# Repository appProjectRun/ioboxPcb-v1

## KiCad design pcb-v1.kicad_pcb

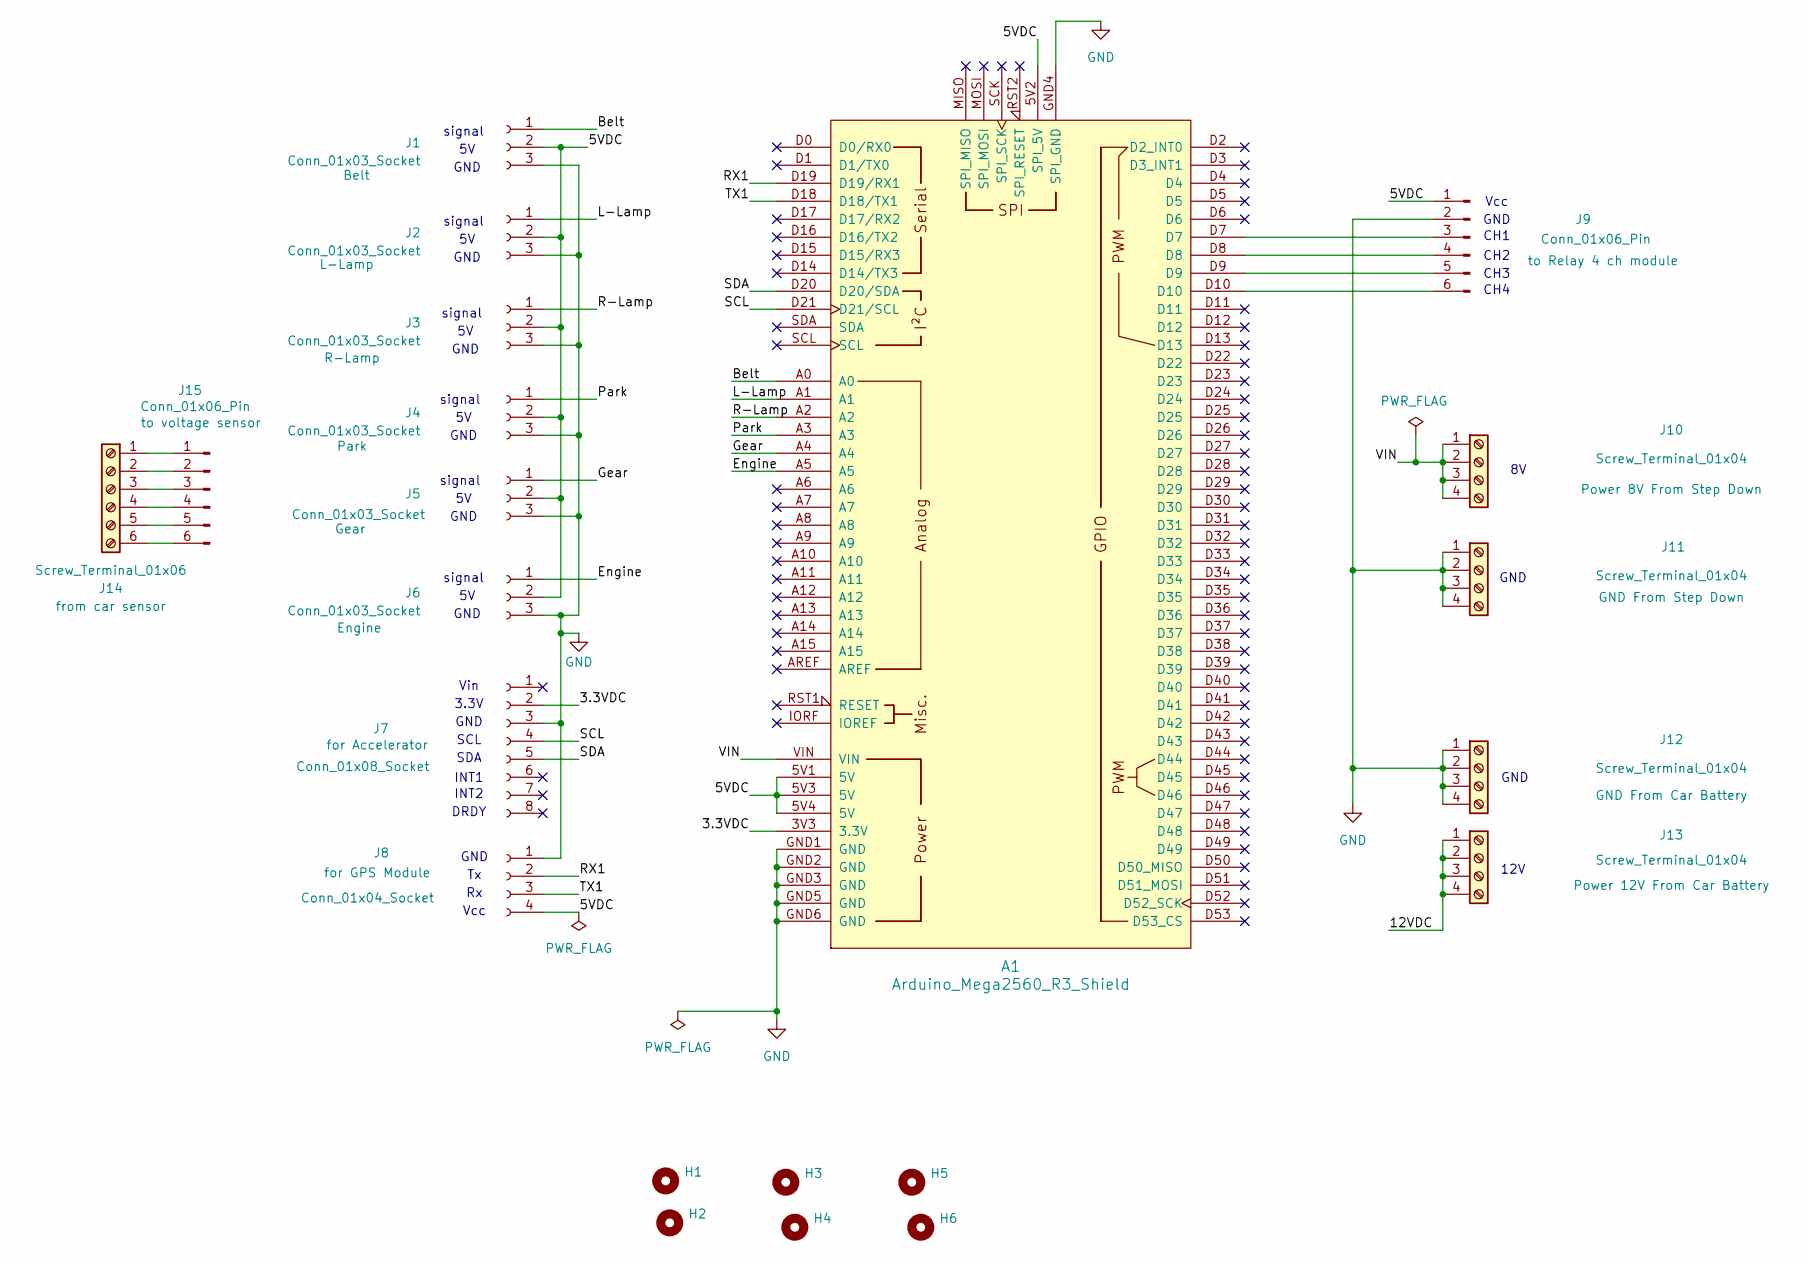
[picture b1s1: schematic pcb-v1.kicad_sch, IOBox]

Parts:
A1: Arduino_Mega2560_R3_Shield
H1, H2, H3, H4, H5, H6: MountingHole; MountingHole_4.5mm
J1, J2, J3, J4, J5, J6: Conn_01x03_Socket; PinSocket_1x03_P2.54mm_Vertical
J7: Conn_01x08_Socket; PinSocket_1x08_P2.54mm_Vertical
J8: Conn_01x04_Socket; PinSocket_1x04_P2.54mm_Vertical
J9, J15: Conn_01x06_Pin; Molex_SPOX_5267-06A_1x06_P2.50mm_Vertical
J10, J11, J12, J13: Screw_Terminal_01x04; TerminalBlock_bornier-4_P5.08mm
J14: Screw_Terminal_01x06; TerminalBlock_bornier-6_P5.08mm

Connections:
/3.3VDC: A1.3V3 (3.3V), J7.2
/5VDC: A1.5V1 (5V), A1.5V2 (SPI_5V), A1.5V3 (5V), A1.5V4 (5V), J1.2, J2.2, J3.2, J4.2, J5.2, J6.2, J8.4, J9.1
/12VDC: J13.1, J13.2, J13.3, J13.4
/Belt: A1.A0, J1.1
/Engine: A1.A5, J6.1
/Gear: A1.A4, J5.1
/L-Lamp: A1.A1, J2.1
/Park: A1.A3, J4.1
/R-Lamp: A1.A2, J3.1
/RX1: A1.D19 (D19/RX1), J8.2
/SCL: A1.D21 (D21/SCL), J7.4
/SDA: A1.D20 (D20/SDA), J7.5
/TX1: A1.D18 (D18/TX1), J8.3
/VIN: A1.VIN, J10.1, J10.2, J10.3, J10.4
GND: A1.GND1 (GND), A1.GND2 (GND), A1.GND3 (GND), A1.GND4 (SPI_GND), A1.GND5 (GND), A1.GND6 (GND), J1.3, J2.3, J3.3, J4.3, J5.3, J6.3, J7.3, J8.1, J9.2, J11.1, J11.2, J11.3, J11.4, J12.1, J12.2, J12.3, J12.4
unnamed: A1.D7, J9.3
unnamed: A1.D8, J9.4
unnamed: A1.D9, J9.5
unnamed: A1.D10, J9.6
unnamed: J14.1, J15.1
unnamed: J14.2, J15.2
unnamed: J14.3, J15.3
unnamed: J14.4, J15.4
unnamed: J14.5, J15.5
unnamed: J14.6, J15.6

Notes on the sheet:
Vcc
CH3
GND
signal
INT1
3.3V
Vin
SCL
DRDY
CH2
CH4
12V
SDA
INT2
CH1

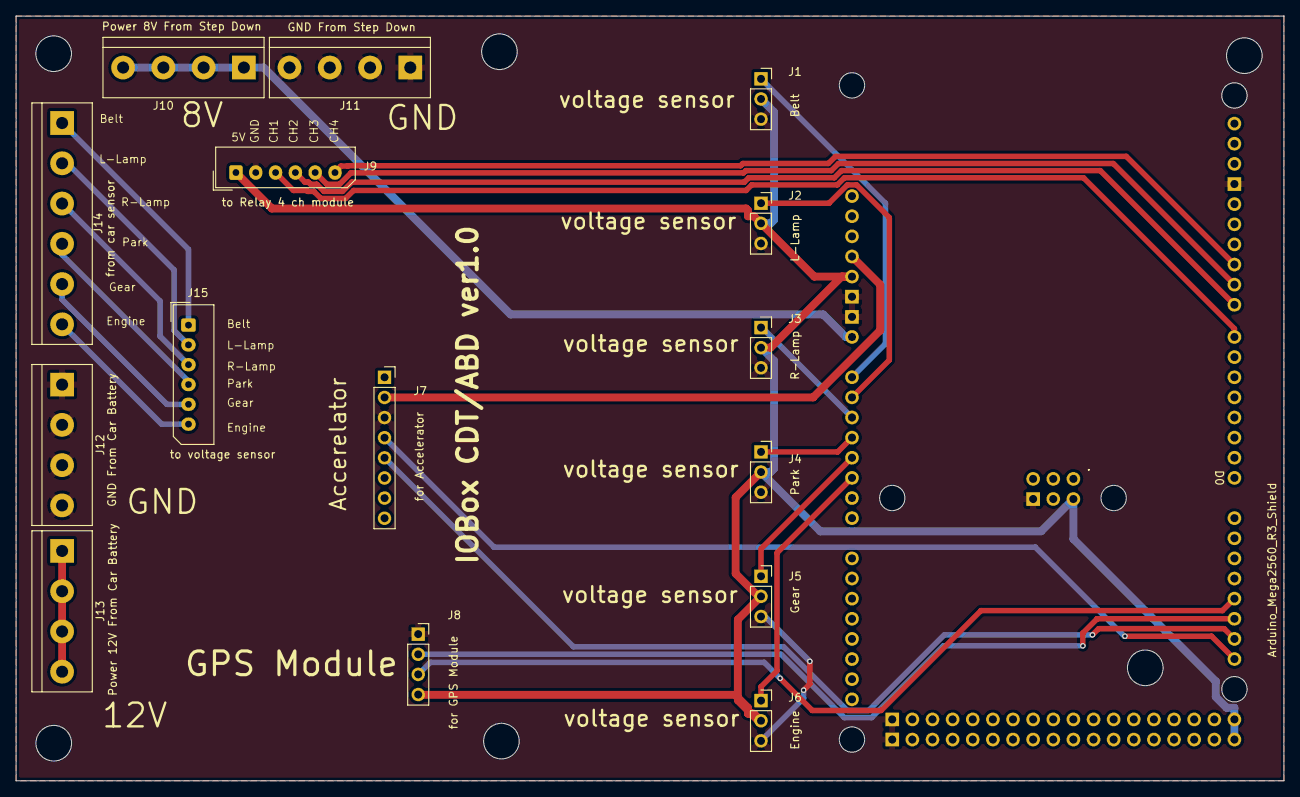
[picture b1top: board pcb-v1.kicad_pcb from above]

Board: 2 copper layers, 160.0 x 96.5 mm, 22 parts (0 on the bottom side), 25 nets.

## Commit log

2026-03-23 add freerouting
2026-03-24 add arduino due symbol
2026-03-25 add voltage sensor pin
2026-03-25 add all symbol and footprint
2026-03-30 before routing
2026-03-30 ver 1.2
2026-03-30 add part finish
2026-03-30 start wiring track
2026-03-30 wiring complete
2026-03-31 change to small pcb
2026-03-31 adjust foot print to small size
2026-03-31 finish pcb
2026-04-01 final
2026-04-01 change ground voltage sensor5 not connected
